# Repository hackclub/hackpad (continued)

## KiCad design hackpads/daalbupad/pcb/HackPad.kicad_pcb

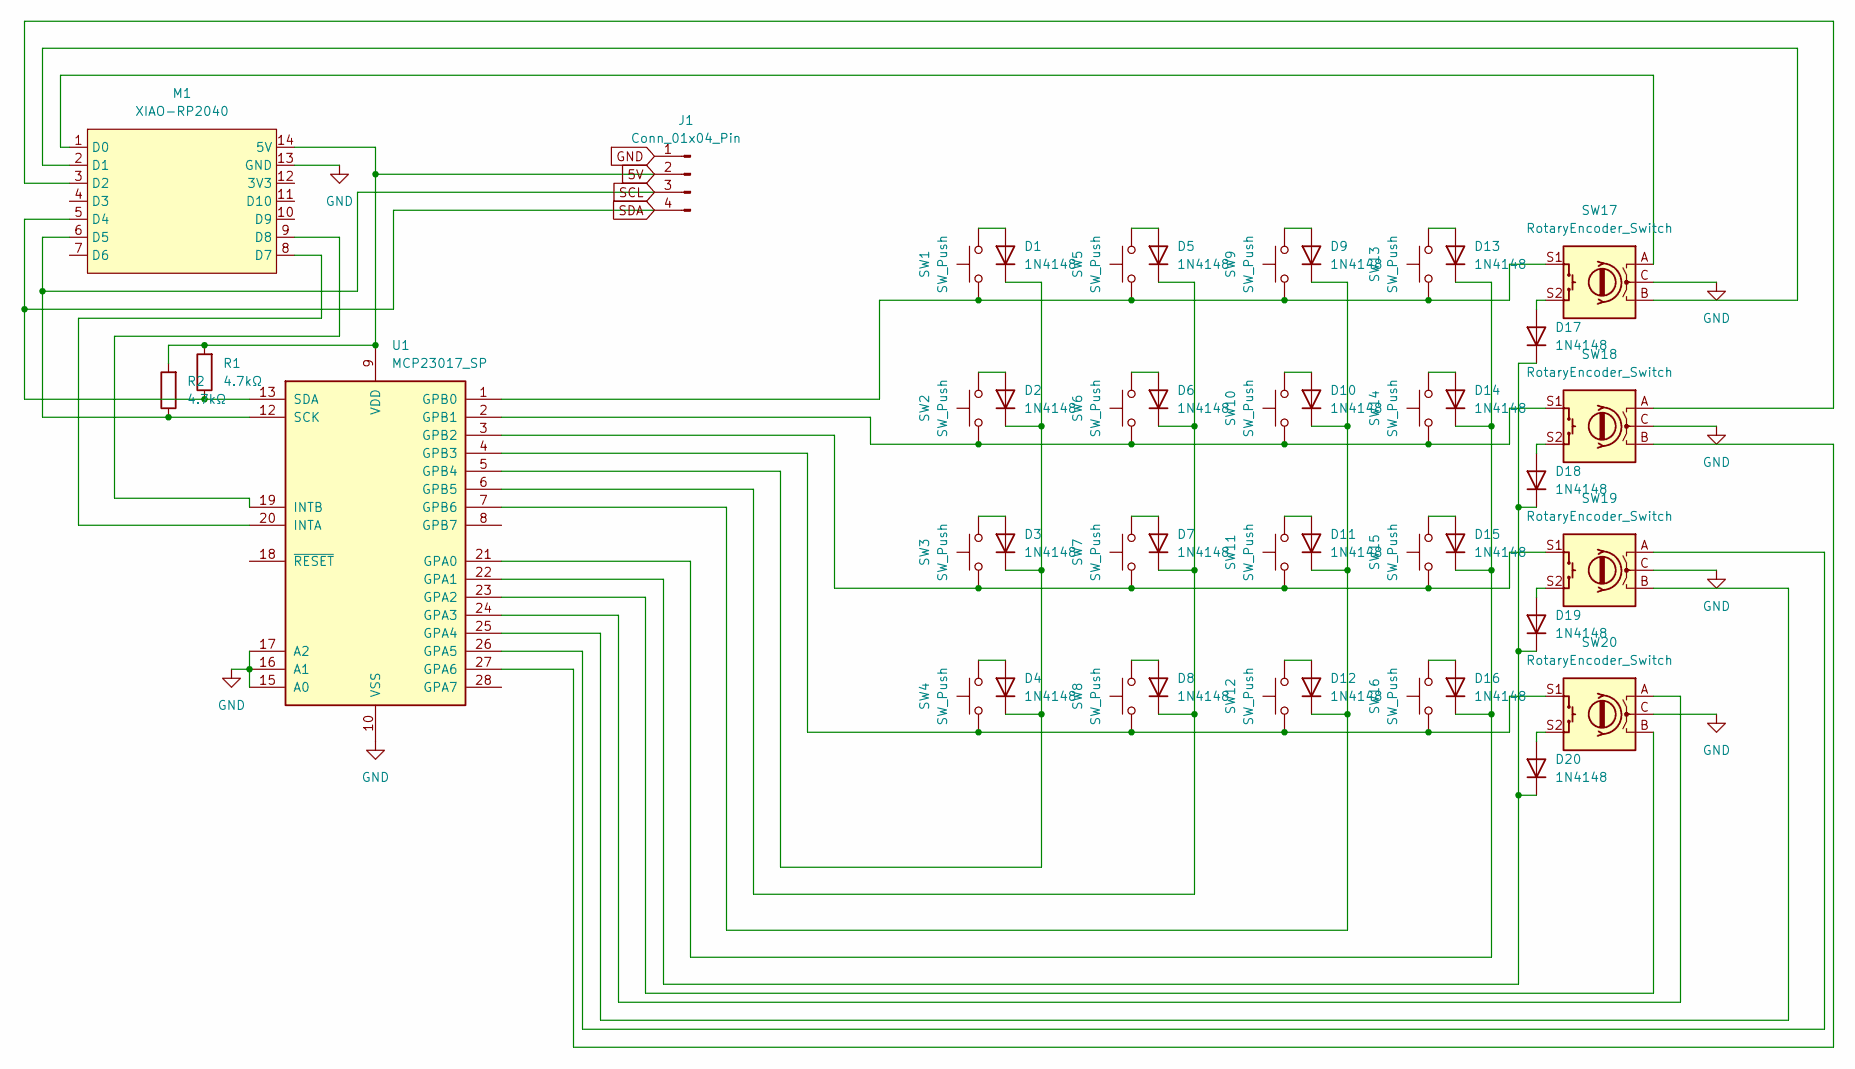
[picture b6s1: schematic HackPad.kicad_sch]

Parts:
D1, D2, D3, D4, D5, D6, D7, D8, D9, D10, D11, D12, D13, D14, D15, D16, D17, D18, D19, D20: 1N4148; D_DO-35_SOD27_P7.62mm_Horizontal
J1: Conn_01x04_Pin; SSD1306-0.91-OLED-4pin-128x32
M1: XIAO-RP2040
R1, R2: 4.7kΩ; R_Axial_DIN0204_L3.6mm_D1.6mm_P5.08mm_Horizontal
SW1, SW2, SW3, SW4, SW5, SW6, SW7, SW8, SW9, SW10, SW11, SW12, SW13, SW14, SW15, SW16: SW_Push; SW_Cherry_MX_1.00u_PCB3d
SW17, SW18, SW19, SW20: RotaryEncoder_Switch; RotaryEncoder_Alps_EC11E-Switch_Vertical_H20mm_CircularMoun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
U1: MCP23017_SP; DIP-28_W7.62mm

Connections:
5V: J1.2, M1.14 (5V), R1.2, R2.2, U1.9 (VDD)
GND: J1.1, M1.13 (GND), SW17.C, SW18.C, SW19.C, SW20.C, U1.10 (VSS), U1.15 (A0), U1.16 (A1), U1.17 (A2)
unnamed: D1.2 (A), SW1.2
unnamed: D1.1 (K), D2.1 (K), D3.1 (K), D4.1 (K), U1.5 (GPB4)
unnamed: D2.2 (A), SW2.2
unnamed: D3.2 (A), SW3.2
unnamed: D4.2 (A), SW4.2
unnamed: D5.2 (A), SW5.2
unnamed: D5.1 (K), D6.1 (K), D7.1 (K), D8.1 (K), U1.6 (GPB5)
unnamed: D6.2 (A), SW6.2
unnamed: D7.2 (A), SW7.2
unnamed: D8.2 (A), SW8.2
unnamed: D9.2 (A), SW9.2
unnamed: D10.2 (A), SW10.2
unnamed: D9.1 (K), D10.1 (K), D11.1 (K), D12.1 (K), U1.7 (GPB6)
unnamed: D11.2 (A), SW11.2
unnamed: D12.2 (A), SW12.2
unnamed: D13.2 (A), SW13.2
unnamed: D13.1 (K), D14.1 (K), D15.1 (K), D16.1 (K), U1.21 (GPA0)
unnamed: D14.2 (A), SW14.2
unnamed: D15.2 (A), SW15.2
unnamed: D16.2 (A), SW16.2
unnamed: D17.2 (A), SW17.S2
unnamed: D17.1 (K), D18.1 (K), D19.1 (K), D20.1 (K), U1.22 (GPA1)
unnamed: D18.2 (A), SW18.S2
unnamed: D19.2 (A), SW19.S2
unnamed: D20.2 (A), SW20.S2
unnamed: M1.1 (D0), SW17.A
unnamed: M1.2 (D1), SW17.B
unnamed: M1.3 (D2), SW18.A
unnamed: M1.8 (D7), U1.20 (INTA)
unnamed: M1.9 (D8), U1.19 (INTB)
unnamed: SW20.B, U1.23 (GPA2)
unnamed: SW20.A, U1.24 (GPA3)
unnamed: SW19.B, U1.25 (GPA4)
unnamed: SW19.A, U1.26 (GPA5)
unnamed: SW18.B, U1.27 (GPA6)
unnamed: SW1.1, SW5.1, SW9.1, SW13.1, SW17.S1, U1.1 (GPB0)
unnamed: SW2.1, SW6.1, SW10.1, SW14.1, SW18.S1, U1.2 (GPB1)
unnamed: SW3.1, SW7.1, SW11.1, SW15.1, SW19.S1, U1.3 (GPB2)
unnamed: SW4.1, SW8.1, SW12.1, SW16.1, SW20.S1, U1.4 (GPB3)
SCL: J1.3, M1.6 (D5), R2.1, U1.12 (SCK)
SDA: J1.4, M1.5 (D4), R1.1, U1.13 (SDA)

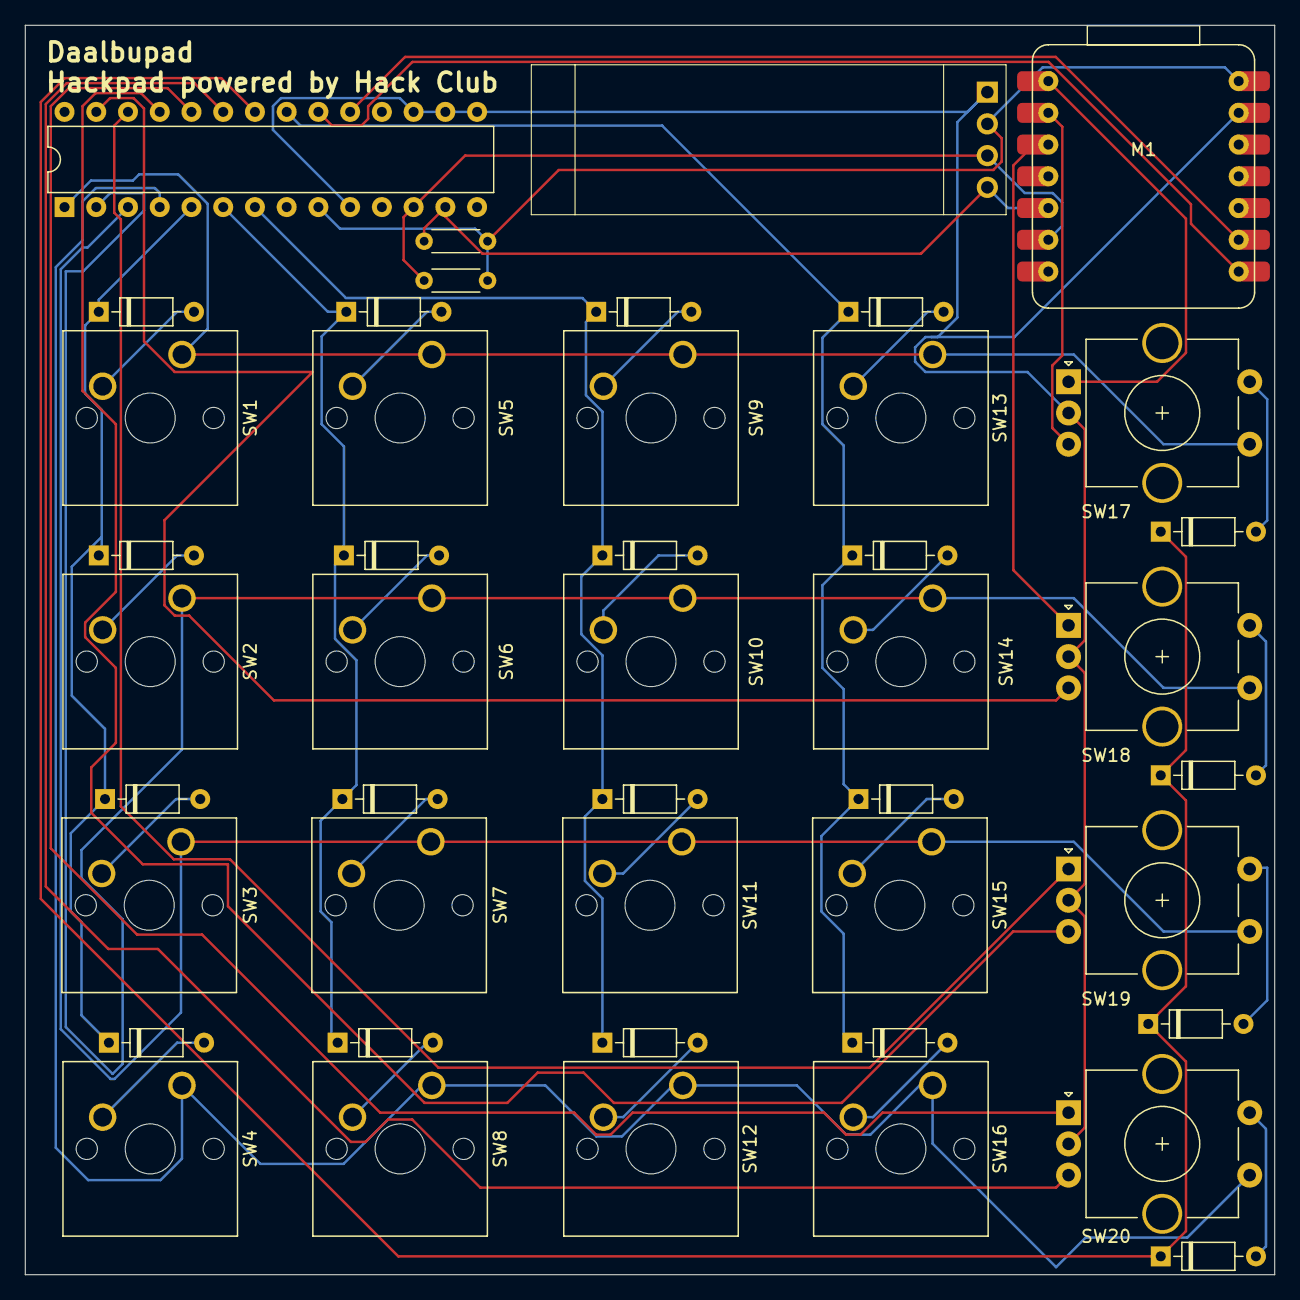
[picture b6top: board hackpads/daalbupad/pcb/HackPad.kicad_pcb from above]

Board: 2 copper layers, 100.0 x 100.0 mm, 45 parts (0 on the bottom side), 43 nets.

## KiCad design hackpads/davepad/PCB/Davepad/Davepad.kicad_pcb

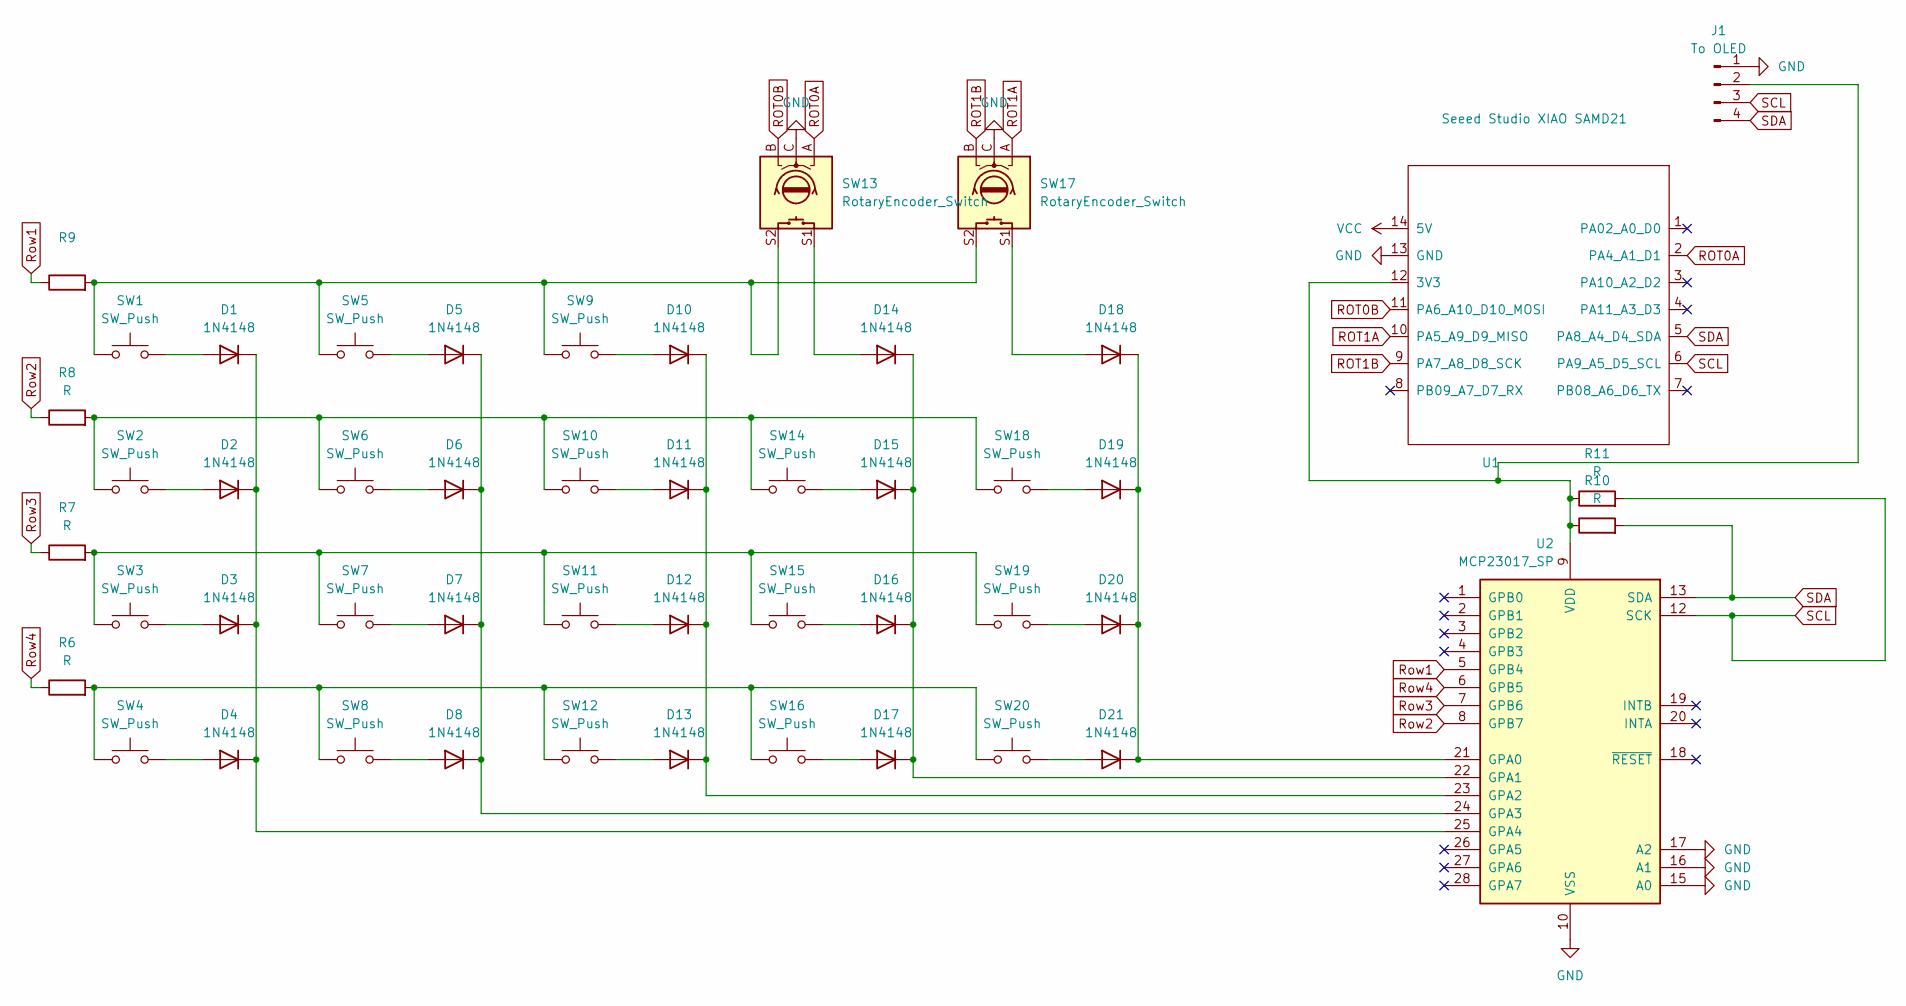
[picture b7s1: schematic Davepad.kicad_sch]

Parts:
D1, D2, D3, D4, D5, D6, D7, D8, D10, D11, D12, D13, D14, D15, D16, D17, D18, D19, D20, D21: 1N4148; D_DO-35_SOD27_P7.62mm_Horizontal
J1: To OLED; PinHeader_1x04_P1.00mm_Vertical
R6, R7, R8, R9, R10, R11: R; R_Axial_DIN0204_L3.6mm_D1.6mm_P7.62mm_Horizontal
SW1, SW2, SW3, SW4, SW5, SW6, SW7, SW8, SW9, SW10, SW11, SW12, SW14, SW15, SW16, SW18, SW19, SW20: SW_Push; SW_Cherry_MX_1.00u_PCB
SW13, SW17: RotaryEncoder_Switch; RotaryEncoder_Alps_EC11E-Switch_Vertical_H20mm
U1: Seeed Studio XIAO SAMD21; XIAO-Generic-Thruhole-14P-2.54-21X17.8MM
U2: MCP23017_SP; DIP-28_W7.62mm

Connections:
GND: J1.1, SW13.C, SW17.C, U1.13 (GND), U2.10 (VSS), U2.15 (A0), U2.16 (A1), U2.17 (A2)
unnamed: D1.2 (A), SW1.2
unnamed: D1.1 (K), D2.1 (K), D3.1 (K), D4.1 (K), U2.25 (GPA4)
unnamed: D2.2 (A), SW2.2
unnamed: D3.2 (A), SW3.2
unnamed: D4.2 (A), SW4.2
unnamed: D5.2 (A), SW5.2
unnamed: D5.1 (K), D6.1 (K), D7.1 (K), D8.1 (K), U2.24 (GPA3)
unnamed: D6.2 (A), SW6.2
unnamed: D7.2 (A), SW7.2
unnamed: D8.2 (A), SW8.2
unnamed: D10.2 (A), SW9.2
unnamed: D10.1 (K), D11.1 (K), D12.1 (K), D13.1 (K), U2.23 (GPA2)
unnamed: D11.2 (A), SW10.2
unnamed: D12.2 (A), SW11.2
unnamed: D13.2 (A), SW12.2
unnamed: D14.2 (A), SW13.S1
unnamed: D14.1 (K), D15.1 (K), D16.1 (K), D17.1 (K), U2.22 (GPA1)
unnamed: D15.2 (A), SW14.2
unnamed: D16.2 (A), SW15.2
unnamed: D17.2 (A), SW16.2
unnamed: D18.2 (A), SW17.S1
unnamed: D18.1 (K), D19.1 (K), D20.1 (K), D21.1 (K), U2.21 (GPA0)
unnamed: D19.2 (A), SW18.2
unnamed: D20.2 (A), SW19.2
unnamed: D21.2 (A), SW20.2
unnamed: J1.2, R10.1, R11.1, U1.12 (3V3), U2.9 (VDD)
unnamed: R6.2, SW4.1, SW8.1, SW12.1, SW16.1, SW20.1
unnamed: R7.2, SW3.1, SW7.1, SW11.1, SW15.1, SW19.1
unnamed: R8.2, SW2.1, SW6.1, SW10.1, SW14.1, SW18.1
unnamed: R9.2, SW1.1, SW5.1, SW9.1, SW13.S2, SW17.S2
ROT0A: SW13.A, U1.2 (PA4_A1_D1)
ROT0B: SW13.B, U1.11 (PA6_A10_D10_MOSI)
ROT1A: SW17.A, U1.10 (PA5_A9_D9_MISO)
ROT1B: SW17.B, U1.9 (PA7_A8_D8_SCK)
Row1: R9.1, U2.5 (GPB4)
Row2: R8.1, U2.8 (GPB7)
Row3: R7.1, U2.7 (GPB6)
Row4: R6.1, U2.6 (GPB5)
SCL: J1.3, R11.2, U1.6 (PA9_A5_D5_SCL), U2.12 (SCK)
SDA: J1.4, R10.2, U1.5 (PA8_A4_D4_SDA), U2.13 (SDA)
VCC: U1.14 (5V)

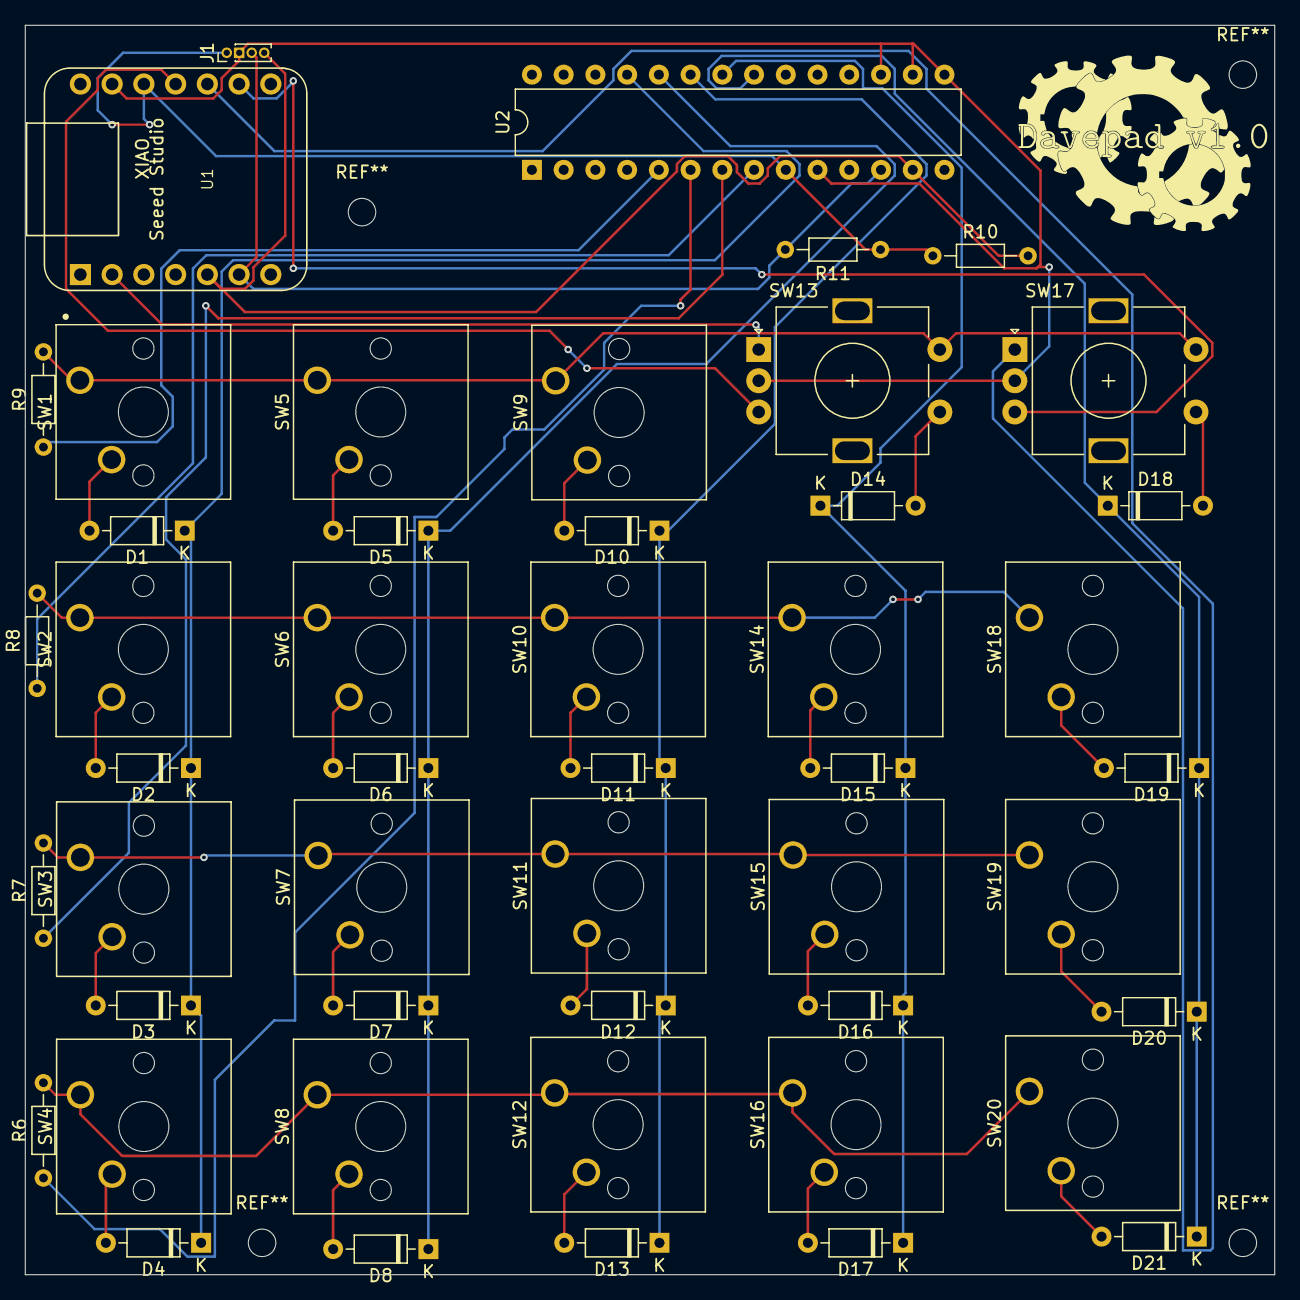
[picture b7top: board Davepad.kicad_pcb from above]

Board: 2 copper layers, 100.0 x 100.0 mm, 49 parts (0 on the bottom side), 41 nets.
